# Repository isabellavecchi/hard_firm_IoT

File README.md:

# hard_firm_IoT
An WiFi connected Sound System with Alarm Clock, and real-time weather info

O projeto de firmware oficial é o wakeNdance. 

A tabela de partição da memoria, que substituí manualmente se encontra na pasta raiz de firmware.

Também foi necessário mudar a configuração de memória manualmente, mudei para 16Mbytes.

Este projeto foi inicializado na disciplina de "Hardware e Firmware - IoT" da UFU, e continuei o desenvolvimento para portifólio.

A placa utilizada foi a ESP32-S3 OTG.

Features:
  
  - Wi-Fi com conexão controlada;
  
  - serviço web construído de forma a dar manutenção facilitada;
  
  - tasks dos botões contruída, mas aguardando a função de leitura do cartão ser concluída, para ter as funcionalidades costuradas;
  
  - freeRTOS, com controle de queue entre tasks;
  
  - servidor HTTP controlando o serviço web;
  
  - back-end e front-end funcionando;
  
  - socket NTP;
  
  - LED atualizando de acordo com o status da conexão;
  
  - display OLED 1306 funcionando, e com funções default, como o botão, aguardando a resolução de bugs do DMA;
  
  - features implementadas no modelo POO.

To finish:
  
  - trocar a saída de som I2S por PDM, pelo fato de o módulo sendo utilizado, não ter tradução de I2S;
  
  - testar o DMA após a saída;
  
  - assim que as 2 camadas supracitadas estiverem funciando adequadamente, convertê-las para POO.

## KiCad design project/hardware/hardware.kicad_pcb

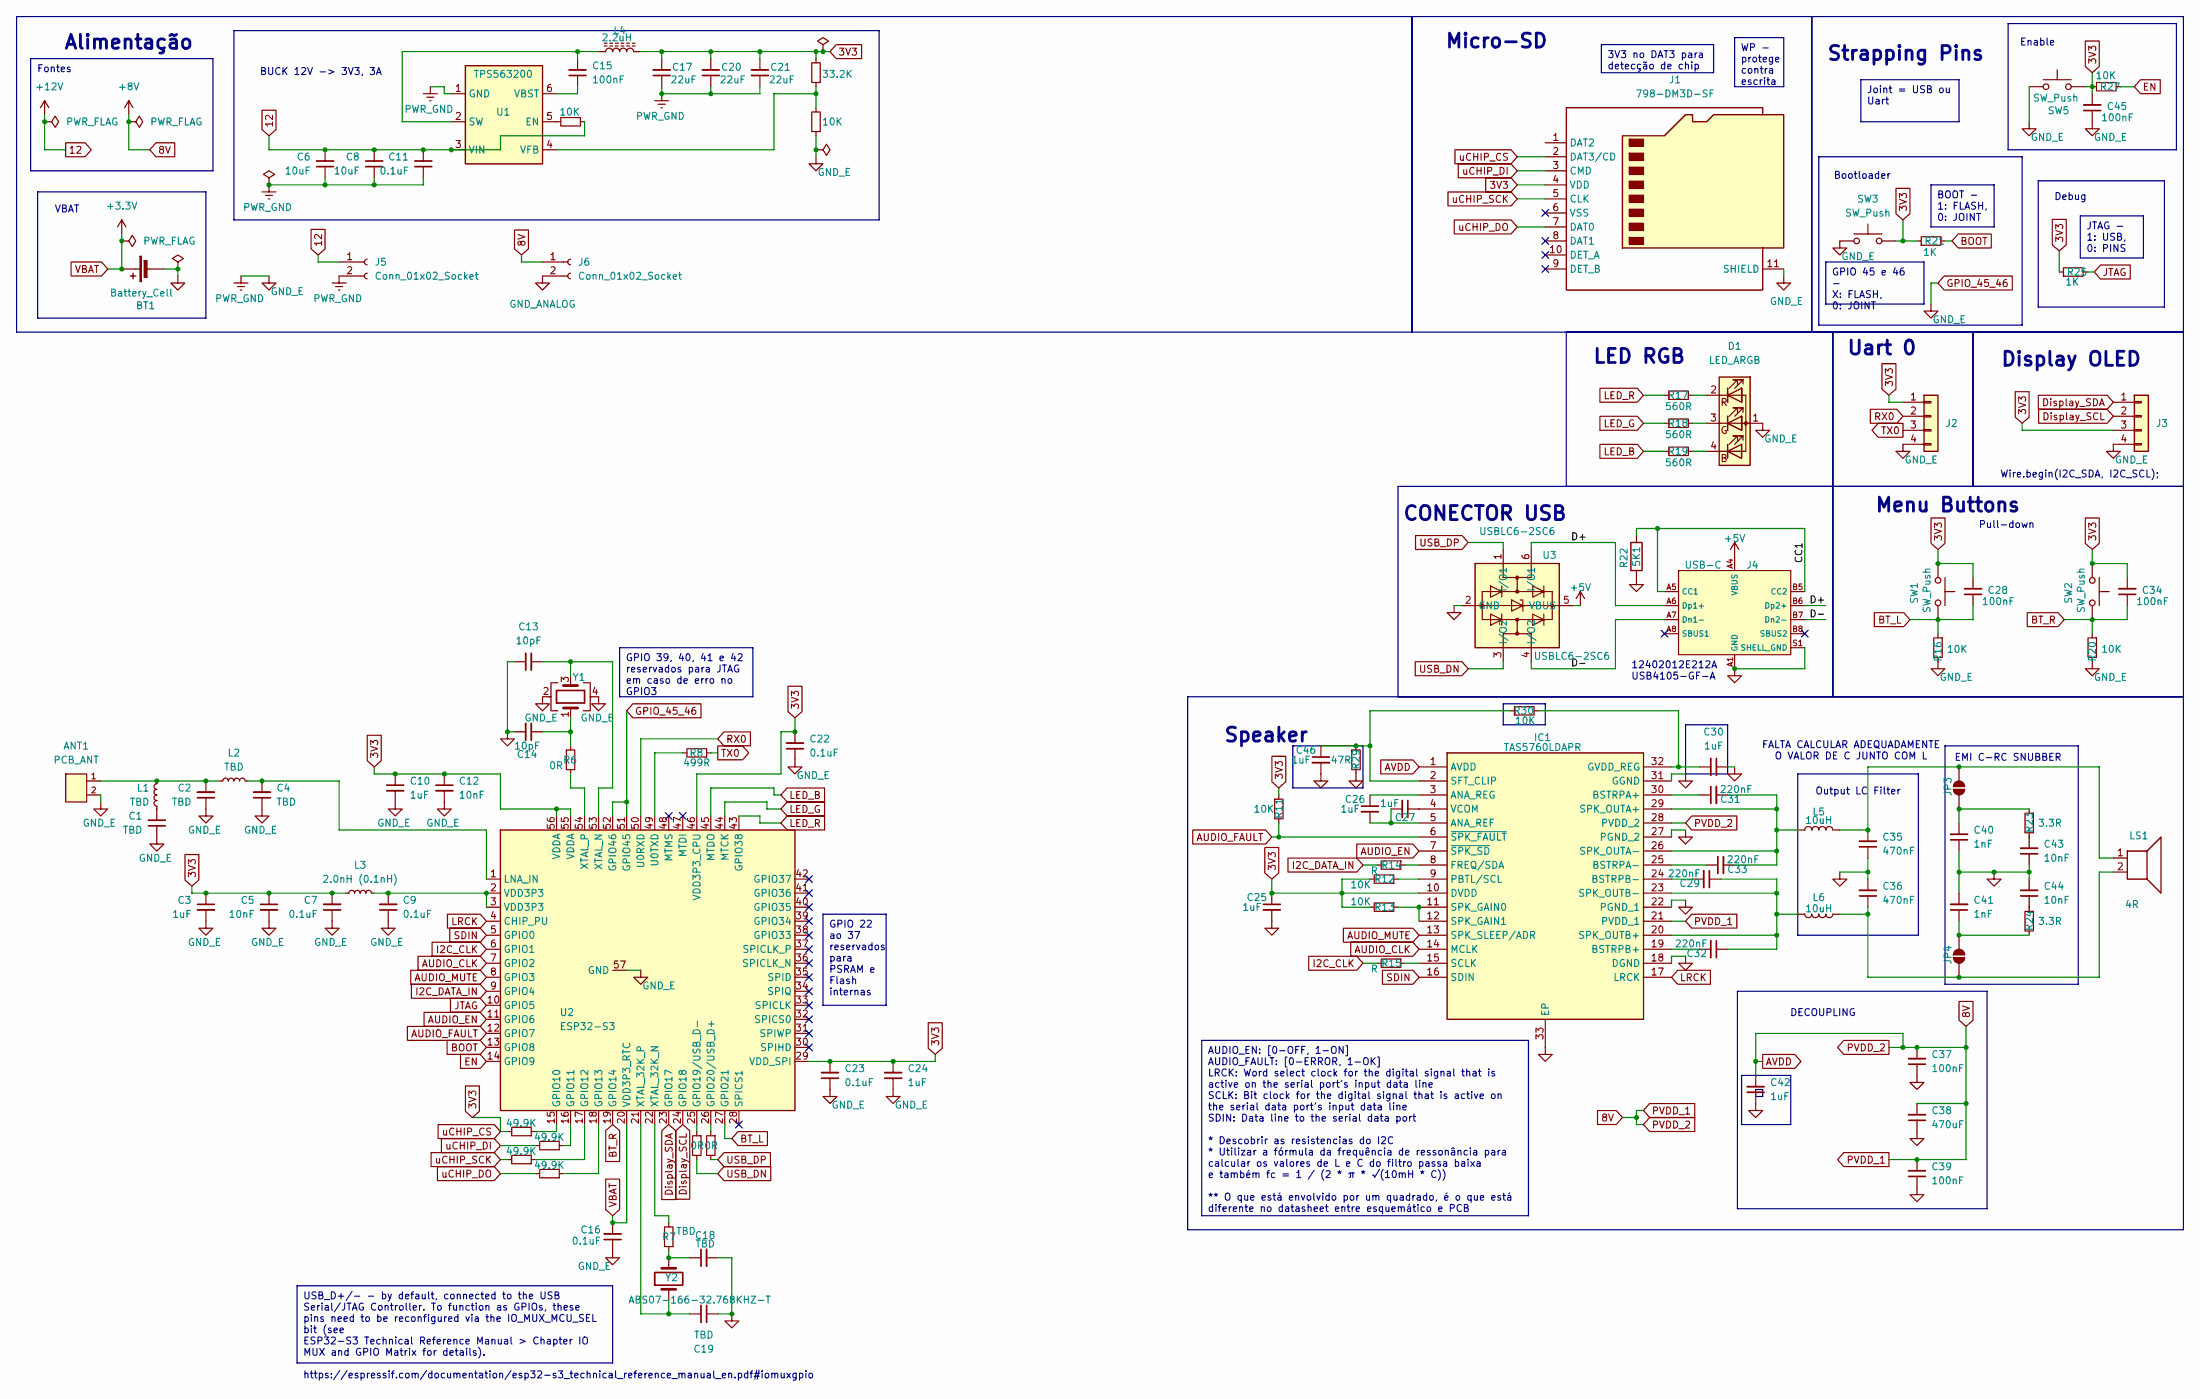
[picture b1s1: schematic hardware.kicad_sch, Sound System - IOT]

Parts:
ANT1: PCB_ANT; Texas_SWRA117D_2.4GHz_Left
BT1: Battery_Cell
C1, C2, C4, C18, C19: TBD; C_0402_1005Metric
C3, C10, C24, C25, C26, C27, C30, C42, C46: 1uF; C_0402_1005Metric
C5, C12, C43, C44: 10nF; C_0402_1005Metric
C6, C8: 10uF; C_0805_2012Metric_Pad1.18x1.45mm_HandSolder
C7, C9, C11, C16, C22, C23: 0.1uF; C_0402_1005Metric
C13, C14: 10pF; C_0402_1005Metric
C15: 100nF; C_0805_2012Metric_Pad1.18x1.45mm_HandSolder
C17, C20, C21: 22uF; C_0603_1608Metric_Pad1.08x0.95mm_HandSolder
C28, C34, C37, C39, C45: 100nF; C_0402_1005Metric
C29, C31, C32, C33: 220nF; C_0402_1005Metric
C35, C36: 470nF; C_0402_1005Metric
C38: 470uF; C_0402_1005Metric
C40, C41: 1nF; C_0402_1005Metric
D1: LED_ARGB; PinSocket_1x04_P1.27mm_Vertical_SMD_Pin1Left
IC1: TAS5760LDAPR; HTSSOP-32-1EP_6.1x11mm_P0.65mm_EP5.2x11mm_Mask4.11x4.36mm_T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; Mouser Part Number 595-TAS5760LDAPR
J1: 798-DM3D-SF; microSD_HC_Hirose_DM3D-SF; Mouser Part Number 523-GMC020080HR
J2, J3: Conn_01x04; PinSocket_1x04_P1.27mm_Vertical_SMD_Pin1Left
J4: USB-C; USB_C_Receptacle_XKB_U262-16XN-4BVC11
J5, J6: Conn_01x02_Socket; PinSocket_2x01_P2.54mm_Vertical_SMD
JP3, JP4: SolderJumper_2_Open; SolderJumper-2_P1.3mm_Open_RoundedPad1.0x1.5mm
L1, L2: TBD; L_0402_1005Metric
L3: 2.0nH (0.1nH); L_0402_1005Metric
L4: 2.2uH; L_TDK_VLS6045EX_VLS6045AF
L5, L6: 10uH; L_0402_1005Metric
LS1: 4R; PinSocket_2x01_P2.54mm_Vertical_SMD
R1, R2, R3, R4: 49.9K; R_0402_1005Metric
R5, R10, R11, R12, R13, R16, R20, R27, R30: 10K; R_0201_0603Metric_Pad0.64x0.40mm_HandSolder
R6, R26, R28: 0R; R_0402_1005Metric
R7: TBD; R_0402_1005Metric
R8: 499R; R_0402_1005Metric
R9: 33.2K; R_0402_1005Metric
R14, R15: R; R_0201_0603Metric_Pad0.64x0.40mm_HandSolder
R17, R18, R19: 560R; R_0402_1005Metric
R21, R25: 1K; R_0402_1005Metric
R22: 5K1; R_0402_1005Metric
R23, R24: 3.3R; R_0402_1005Metric
R29: 47R; R_0201_0603Metric_Pad0.64x0.40mm_HandSolder
SW1, SW2, SW3, SW5: SW_Push; SW_SPST_PTS810
U1: TPS563200; SOT-23-6
U2: ESP32-S3; QFN-56-1EP_7x7mm_P0.4mm_EP4x4mm
U3: USBLC6-2SC6; SOT95P280X145-6N
Y1: ECS-400-10-36B2-CKM-TR; Crystal_SMD_2520-4Pin_2.5x2.0mm
Y2: ABS07-166-32.768KHZ-T; Crystal_SMD_MicroCrystal_CC7V-T1A-2Pin_3.2x1.5mm_HandSolder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

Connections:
3V3: C3.1, C5.1, C7.2, C10.1, C12.1, C17.2, C20.2, C21.2, C22.2, C23.2, C24.2, C25.1, C28.2, C34.2, C45.2, IC1.10 (DVDD), J1.2 (DAT3/CD), J1.4 (VDD), J2.1, J3.3, L3.1, L4.2, R1.2, R9.2, R11.1, R12.2, R13.2, R21.1, R25.1, R27.1, SW1.1, SW2.1, SW3.2, SW5.2, U2.29 (VDD_SPI), U2.46 (VDD3P3_CPU), U2.55 (VDDA), U2.56 (VDDA)
8V: C37.2, C38.2, C39.2, C42.2, IC1.1 (AVDD), IC1.21 (PVDD_1), IC1.28 (PVDD_2), J6.1
12: C6.2, C8.2, C11.2, J5.1, R5.1, U1.3 (VIN)
+5V: J4.A4 (VBUS), J4.A9 (VBUS), J4.B4 (VBUS), J4.B9 (VBUS), U3.5 (VBUS)
/CC1: J4.A5 (CC1), J4.B5 (CC2), R22.1
/D+: J4.A6 (Dp1+), J4.B6 (Dp2+), U3.6 (I/O1)
/D-: J4.A7 (Dn1-), J4.B7 (Dn2-), U3.4 (I/O2)
AUDIO_CLK: IC1.14 (MCLK), U2.7 (GPIO2)
AUDIO_EN: IC1.7 (~SPK_SD), U2.11 (GPIO6)
AUDIO_FAULT: IC1.6 (~SPK_FAULT), R11.2, U2.12 (GPIO7)
AUDIO_MUTE: IC1.13 (SPK_SLEEP/ADR), U2.8 (GPIO3)
BOOT: R21.2, U2.13 (GPIO8)
BT_L: C28.1, R16.1, SW1.2, U2.27 (GPIO21)
BT_R: C34.1, R20.1, SW2.2, U2.19 (GPIO14)
Display_SCL: J3.2, U2.24 (GPIO18)
Display_SDA: J3.1, U2.23 (GPIO17)
EN: R27.2, U2.14 (GPIO9)
GND: BT1.2 (-), C13.1, C14.2, C18.2, C19.1, C25.2, C46.2, J4.A1 (GND), J4.A12 (GND), J4.B1 (GND), J4.B12 (GND), J4.S1 (SHELL_GND), R22.2, R29.2, U3.2 (GND)
GND_ANALOG: C30.1, C35.1, C36.2, C37.1, C38.1, C39.1, C40.1, C41.2, C42.1, C43.1, C44.2, IC1.18 (DGND), IC1.22 (PGND_1), IC1.27 (PGND_2), IC1.31 (GGND), IC1.33 (EP), J6.2
GPIO_45_46: ANT1.2, C1.1, C2.1, C3.2, C4.1, C5.2, C6.1, C7.1, C8.1, C9.1, C10.2, C11.1, C12.2, C16.1, C17.1, C20.1, C21.1, C22.1, C23.1, C24.1, C45.1, D1.1 (A), J1.11 (SHIELD), J2.4, J3.4, J5.2, R10.1, R16.2, R20.2, SW3.1, SW5.1, U1.1 (GND), U2.51 (GPIO45), U2.52 (GPIO46), U2.57 (GND), Y1.2, Y1.4
I2C_CLK: R15.2, U2.6 (GPIO1)
I2C_DATA_IN: R14.2, U2.9 (GPIO4)
JTAG: R25.2, U2.10 (GPIO5)
LED_B: R19.1, U2.45 (MTDO)
LED_G: R18.1, U2.44 (MTCK)
LED_R: R17.1, U2.43 (GPIO38)
LRCK: IC1.17 (LRCK), U2.4 (CHIP_PU)
unnamed: ANT1.1, C2.2, L1.1, L2.1
unnamed: C1.2, L1.2
unnamed: C9.2, L3.2, U2.2 (VDD3P3), U2.3 (VDD3P3)
unnamed: C14.1, R6.1, Y1.1
unnamed: C18.1, R7.1, Y2.2
unnamed: C43.2, R23.2
unnamed: C44.1, R24.1
unnamed: D1.4 (BK), R19.2
unnamed: D1.3 (GK), R18.2
unnamed: D1.2 (RK), R17.2
unnamed: C26.2, C27.2, IC1.5 (ANA_REF)
unnamed: C26.1, IC1.3 (ANA_REG)
unnamed: C31.1, IC1.30 (BSTRPA+)
unnamed: C33.1, IC1.25 (BSTRPA-)
unnamed: C32.2, IC1.19 (BSTRPB+)
unnamed: C29.2, IC1.24 (BSTRPB-)
unnamed: IC1.8 (FREQ/SDA), R14.1
unnamed: C30.2, IC1.32 (GVDD_REG), R30.2
unnamed: IC1.9 (PBTL/SCL), R12.1
unnamed: IC1.15 (SCLK), R15.1
unnamed: C46.1, IC1.2 (SFT_CLIP), R29.1, R30.1
unnamed: IC1.11 (SPK_GAIN0), IC1.12 (SPK_GAIN1), R13.1
unnamed: C31.2, C33.2, IC1.26 (SPK_OUTA-), IC1.29 (SPK_OUTA+), L5.1
unnamed: C29.1, C32.1, IC1.20 (SPK_OUTB+), IC1.23 (SPK_OUTB-), L6.1
unnamed: C27.1, IC1.4 (VCOM)
unnamed: C40.2, JP3.1 (A), R23.1
unnamed: C35.2, JP3.2 (B), L5.2, LS1.1
unnamed: C36.1, JP4.1 (A), L6.2, LS1.2
unnamed: C41.1, JP4.2 (B), R24.2
unnamed: R5.2, U1.5 (EN)
unnamed: C15.2, L4.1, U1.2 (SW)
unnamed: C15.1, U1.6 (VBST)
unnamed: R9.1, R10.2, U1.4 (VFB)
unnamed: R1.1, U2.15 (GPIO10)
unnamed: R3.1, U2.16 (GPIO11)
unnamed: R2.1, U2.17 (GPIO12)
unnamed: R4.1, U2.18 (GPIO13)
unnamed: R26.1, U2.25 (GPIO19/USB_D-)
unnamed: R28.1, U2.26 (GPIO20/USB_D+)
unnamed: C4.2, L2.2, U2.1 (LNA_IN)
unnamed: R8.2, U2.49 (U0TXD)
unnamed: R7.2, U2.22 (XTAL_32K_N)
unnamed: C19.2, U2.21 (XTAL_32K_P), Y2.1
unnamed: C13.2, U2.53 (XTAL_N), Y1.3
unnamed: R6.2, U2.54 (XTAL_P)
RX0: J2.2, U2.50 (U0RXD)
SDIN: IC1.16 (SDIN), U2.5 (GPIO0)
TX0: J2.3, R8.1
USB_DN: R26.2, U3.3 (I/O2)
USB_DP: R28.2, U3.1 (I/O1)
VBAT: BT1.1 (+), C16.2, U2.20 (VDD3P3_RTC)
uCHIP_DI: J1.3 (CMD), R3.2
uCHIP_DO: J1.7 (DAT0), R4.2
uCHIP_SCK: J1.5 (CLK), R2.2

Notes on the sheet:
WP - protege contra escrita
Joint = USB ou Uart
GPIO 39, 40, 41 e 42 reservados para JTAG em caso de erro no GPIO3
USB_D+/- - by default, connected to the USB Serial/JTAG Controller. To function as GPIOs, these pins need to be reconfigured via the IO_MUX_MCU_SEL bit (see ESP32-S3 Technical Reference Manual > Chapter IO MUX and GPIO Matrix for details). https://espressif.com/documentation/esp32-s3_technical_refe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
AUDIO_EN: [0-OFF, 1-ON] AUDIO_FAULT: [0-ERROR, 1-OK] LRCK: Word select clock for the digital signal that is active on the serial port's input data line SCLK: Bit clock for the digital signal that is active on the serial data port's input data line SDIN: Data line to the serial data port * Descobrir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
JTAG - 1: USB, 0: PINS
GPIO 45 e 46 - X: FLASH, 0: JOINT
BOOT - 1: FLASH, 0: JOINT
GPIO 22 ao 37 reservados para PSRAM e Flash internas
3V3 no DAT3 para detecção de chip
Micro-SD
LED RGB
EMI C-RC SNUBBER
Display OLED
Wire.begin(I2C_SDA, I2C_SCL);
Enable
Menu Buttons
FALTA CALCULAR ADEQUADAMENTE O VALOR DE C JUNTO COM L
Bootloader
CONECTOR USB
VBAT
DECOUPLING
Pull-down
BUCK 12V -> 3V3, 3A
Speaker
12402012E212A USB4105-GF-A
Strapping Pins
Alimentação
Debug
Uart 0
Output LC Filter
Fontes

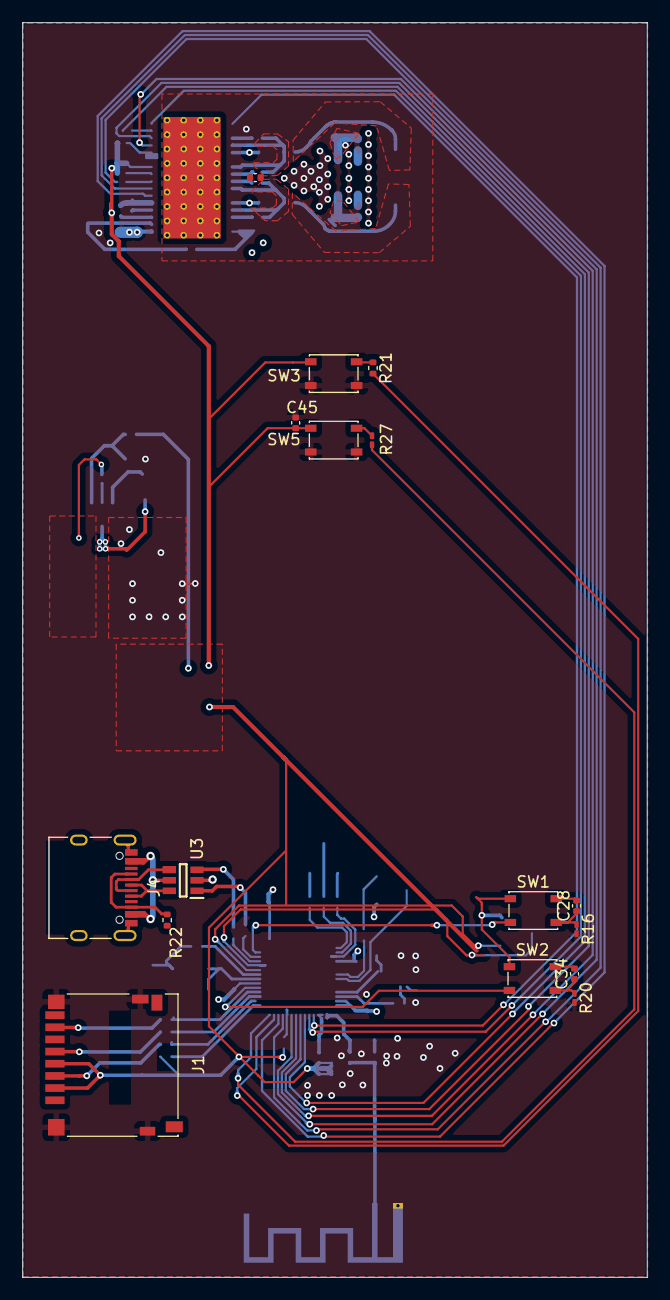
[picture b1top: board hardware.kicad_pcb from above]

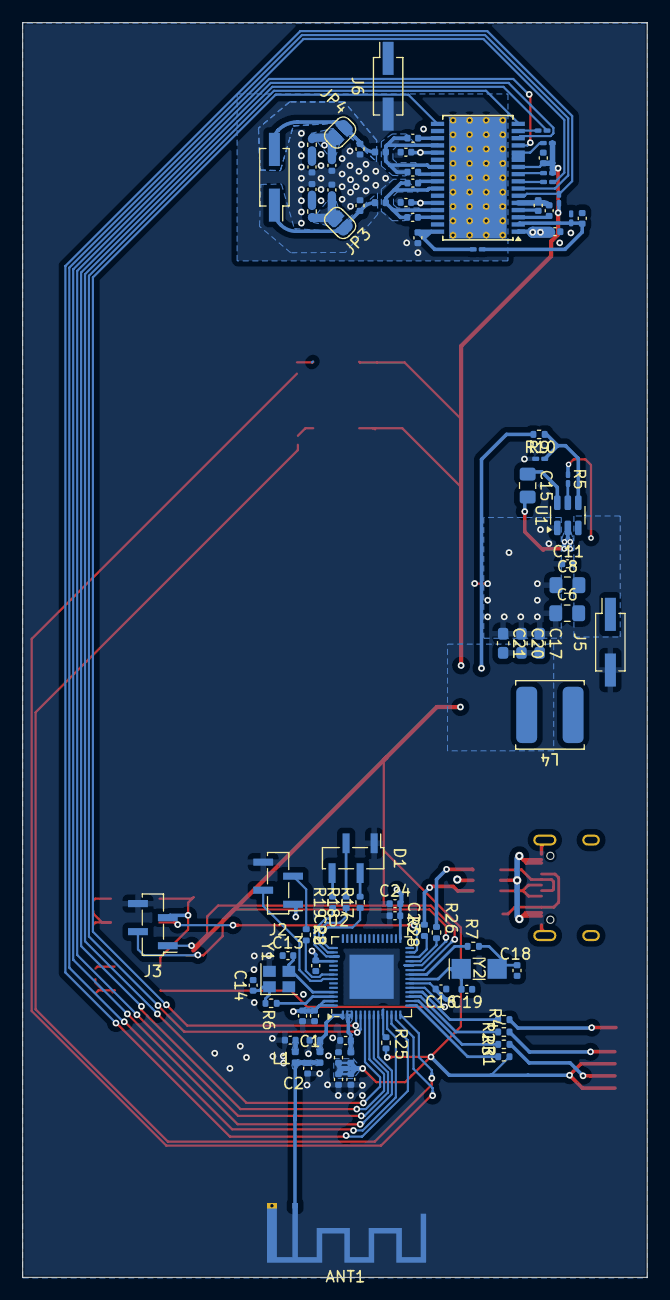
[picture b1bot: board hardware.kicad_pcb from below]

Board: 4 copper layers, 56.5 x 113.5 mm, 103 parts (87 on the bottom side), 81 nets.

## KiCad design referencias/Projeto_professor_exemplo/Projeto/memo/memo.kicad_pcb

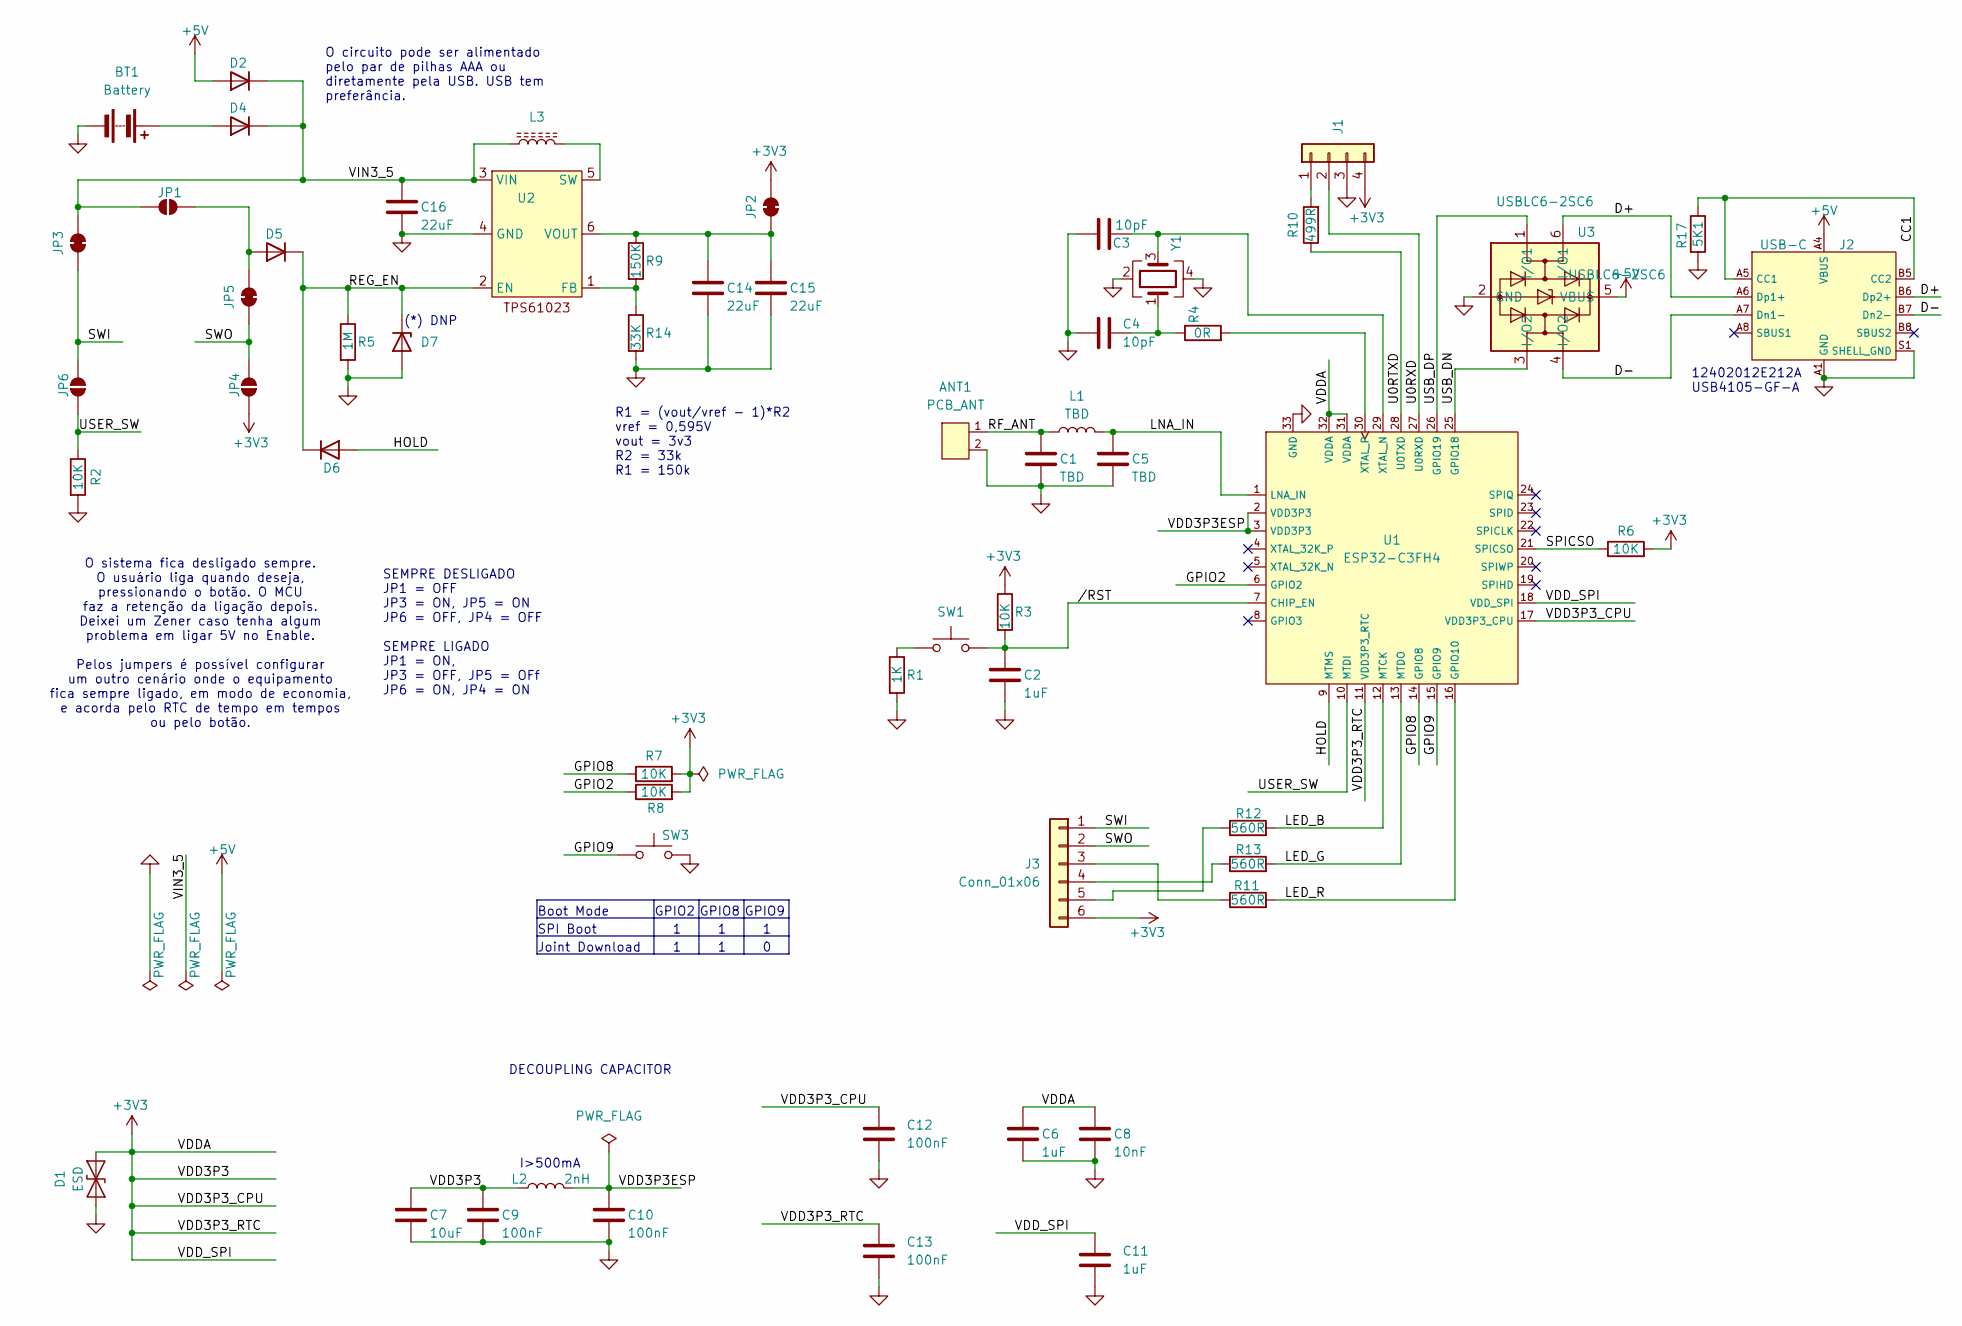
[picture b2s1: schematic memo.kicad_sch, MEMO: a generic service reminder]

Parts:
ANT1: PCB_ANT; Texas_SWRA117D_2.4GHz_Left
BT1: Battery; BatteryHolder_2xAAA
C1, C5: TBD; C_0402_1005Metric
C2, C6, C11: 1uF; C_0402_1005Metric
C3, C4: 10pF; C_0402_1005Metric
C7: 10uF; C_0603_1608Metric
C8: 10nF; C_0402_1005Metric
C9, C10, C12, C13: 100nF; C_0402_1005Metric
C14, C15, C16: 22uF; C_0603_1608Metric
D1: ESD; D_SOD-923
D2, D4, D5, D6, D7: D; D_SOD-123
J1: Conn_01x04; PinHeader_1x04_P1.27mm_Vertical
J2: USB-C; USB_C_Receptacle_XKB_U262-16XN-4BVC11
J3: Conn_01x06; PinHeader_1x06_P1.27mm_Vertical
JP1, JP4, JP6: SolderJumper_2_Open; SolderJumper-2_P1.3mm_Open_RoundedPad1.0x1.5mm
JP2, JP3, JP5: SolderJumper_2_Bridged; SolderJumper-2_P1.3mm_Bridged_RoundedPad1.0x1.5mm
L1: TBD; L_0402_1005Metric
L2: 2nH; L_0402_1005Metric
L3: L_Ferrite; XEL4030101MED
R1: 1K; R_0603_1608Metric
R2, R3, R6, R7, R8: 10K; R_0402_1005Metric
R4: 0R; R_0402_1005Metric
R5: 1M; R_0402_1005Metric
R9: 150K; R_0402_1005Metric
R10: 499R; R_0603_1608Metric
R11, R12, R13: 560R; R_0402_1005Metric
R14: 33K; R_0402_1005Metric
R17: 5K1; R_0402_1005Metric
SW1, SW3: SW_Push; SW_SPST_PTS810
U1: ESP32-C3FH4; QFN50P500X500X90-33N-D
U2: SOT-563
U3: USBLC6-2SC6; SOT95P280X145-6N
Y1: ECS-400-10-36B2-CKM-TR; Crystal_SMD_2520-4Pin_2.5x2.0mm

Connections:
+3V3: C6.1, C7.1, C8.1, C9.1, C11.1, C12.1, C13.1, D1.2 (A2), J1.4, J3.6, JP2.2 (B), JP4.1 (A), L2.1, R3.1, R6.2, R7.2, R8.2, U1.11 (VDD3P3_RTC), U1.17 (VDD3P3_CPU), U1.18 (VDD_SPI), U1.31 (VDDA), U1.32 (VDDA)
+5V: D2.2 (A), J2.A4 (VBUS), J2.A9 (VBUS), J2.B4 (VBUS), J2.B9 (VBUS), U3.5 (VBUS)
/CC1: J2.A5 (CC1), J2.B5 (CC2), R17.1
/D+: J2.A6 (Dp1+), J2.B6 (Dp2+), U3.6 (I/O1)
/D-: J2.A7 (Dn1-), J2.B7 (Dn2-), U3.4 (I/O2)
/GPIO2: R8.1, U1.6 (GPIO2)
/GPIO8: R7.1, U1.14 (GPIO8)
/GPIO9: SW3.1, U1.15 (GPIO9)
/HOLD: D6.2 (A), U1.9 (MTMS)
/LED_B: R12.2, U1.12 (MTCK)
/LED_G: R13.2, U1.13 (MTDO)
/LED_R: R11.2, U1.16 (GPIO10)
/LNA_IN: C5.1, L1.2, U1.1 (LNA_IN)
/REG_EN: D5.1 (K), D6.1 (K), D7.1 (K), R5.1, U2.2 (EN)
/RF_ANT: ANT1.1, C1.1, L1.1
/SPICSO: R6.1, U1.21 (SPICSO)
/SWI: J3.1, JP3.1 (A), JP6.2 (B)
/SWO: J3.2, JP4.2 (B), JP5.1 (A)
/U0RTXD: R10.1, U1.28 (U0TXD)
/U0RXD: J1.2, U1.27 (U0RXD)
/USB_DN: U1.25 (GPIO18), U3.3 (I/O2)
/USB_DP: U1.26 (GPIO19), U3.1 (I/O1)
/USER_SW: JP6.1 (A), R2.1, U1.10 (MTDI)
/VDD3P3ESP: C10.1, L2.2, U1.2 (VDD3P3), U1.3 (VDD3P3)
/VIN3_5: C16.1, D2.1 (K), D4.1 (K), JP1.1 (A), JP3.2 (B), L3.1, U2.3 (VIN)
//RST: C2.1, R3.2, SW1.2, U1.7 (CHIP_EN)
GND: ANT1.2, BT1.2 (-), C1.2, C2.2, C3.1, C4.2, C5.2, C6.2, C7.2, C8.2, C9.2, C10.2, C11.2, C12.2, C13.2, C14.2, C15.2, C16.2, D1.1 (A1), D7.2 (A), J1.3, J2.A1 (GND), J2.A12 (GND), J2.B1 (GND), J2.B12 (GND), J2.S1 (SHELL_GND), R1.2, R2.2, R5.2, R14.2, R17.2, SW3.2, U1.33 (GND), U2.4 (GND), U3.2 (GND), Y1.2, Y1.4
unnamed: BT1.1 (+), D4.2 (A)
unnamed: C4.1, R4.1, Y1.1
unnamed: D5.2 (A), JP1.2 (B), JP5.2 (B)
unnamed: J1.1, R10.2
unnamed: J3.3, R11.1
unnamed: J3.4, R13.1
unnamed: J3.5, R12.1
unnamed: C14.1, C15.1, JP2.1 (A), R9.1, U2.6 (VOUT)
unnamed: R1.1, SW1.1
unnamed: C3.2, U1.29 (XTAL_N), Y1.3
unnamed: R4.2, U1.30 (XTAL_P)
unnamed: R9.2, R14.1, U2.1 (FB)
unnamed: L3.2, U2.5 (SW)

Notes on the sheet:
12402012E212A USB4105-GF-A
SPI Boot
R1 = (vout/vref - 1)*R2 vref = 0,595V vout = 3v3 R2 = 33k R1 = 150k
O sistema fica desligado sempre. O usuário liga quando deseja, pressionando o botão. O MCU faz a retenção da ligação depois. Deixei um Zener caso tenha algum problema em ligar 5V no Enable. Pelos jumpers é possível configurar um outro cenário onde o equipamento fica sempre ligado, em modo de econom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
Joint Download
I>500mA
GPIO2
(*) DNP
SEMPRE DESLIGADO JP1 = OFF JP3 = ON, JP5 = ON JP6 = OFF, JP4 = OFF SEMPRE LIGADO JP1 = ON, JP3 = OFF, JP5 = OFf JP6 = ON, JP4 = ON
Boot Mode
GPIO8
DECOUPLING CAPACITOR
GPIO9
O circuito pode ser alimentado pelo par de pilhas AAA ou diretamente pela USB. USB tem preferância.

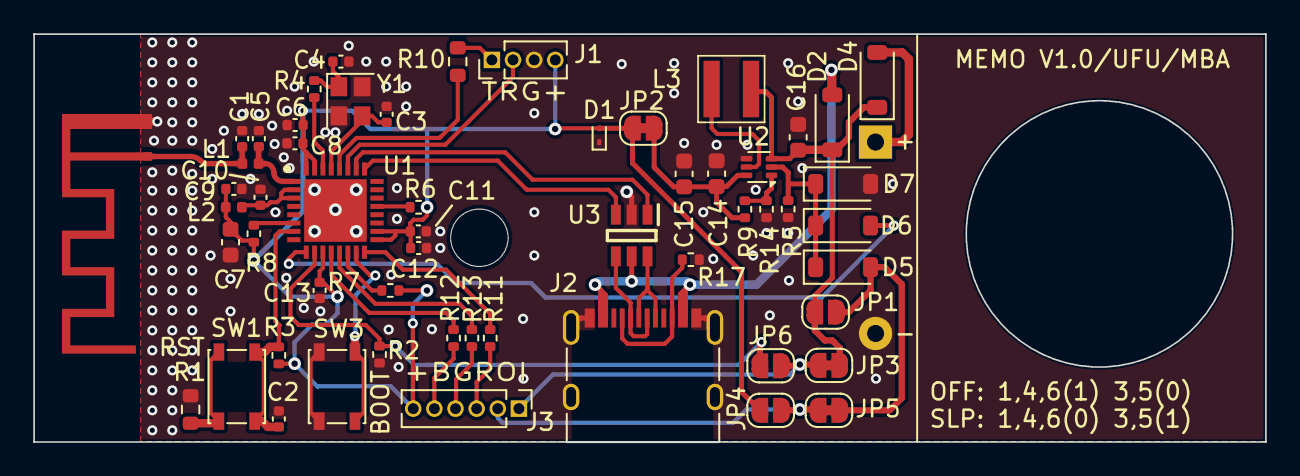
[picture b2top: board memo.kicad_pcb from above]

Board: 4 copper layers, 74.0 x 24.5 mm, 57 parts (1 on the bottom side), 40 nets.

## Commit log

2024-09-25 some drafts I would like to keep - 2 sounds amplifiers; external flash and PSRAM; and the beggining of a buck converter
2024-09-25 schematic - faltando o RTC clock, e conectar os I2C's num so canal
2024-09-30 atualizando alguns footprints; começando o desenho da placa
2024-10-01 RTC footprint; removed 2 buttons, an will remove more stuff to get the USB back
2024-10-05 esquemático com JTAG usb adicionada; preferi deixar o monitor numa i2c separada da i2c do amplificador de audio - para nao correr o risco de ao diminuir o volume buggar a tela
2024-10-06 sound components placed - there were some differences between layout and schematic on the amplifier documentation. They are emphasized by squares on schematic
2024-10-06 roteamentos do amplificador, perifericos agrupados
2024-10-06 desacoplamento
2024-10-06 cartao de memoria e usb
2024-10-07 coloquei a antena para cima para liberar espaço para o amplificador de som; adicionei algumas vias de terra
2024-10-07 realocando estruturas
2024-10-07 footprint socket 01x04 atualizado - partiu casa
2024-10-07 antes da aula
2024-10-07 codigo teste da aula passada
2024-10-07 mudando a estrutura de arquivos e adicionando o projeto hello_world no repositorio de aulas
2024-10-07 agora sim, dei commit da pasta errada
2024-10-08 colocando um projeto RTOS dentro do exemplo da esp
2024-10-26 trying out the s3 board
2024-10-30 structure of project
2024-11-08 adding refs
2024-11-09 wifi conectando
2024-11-09 separating the model_main, so that it is not the main anymore
2024-11-09 removing some tests that went wrong...
2024-11-18 codigo wakeNdance versao 3, com freeRTOS
2024-11-19 get wifi credentials
2024-11-19 curso na udemy sobre ESP-IDF IOT com freeRTOS
2024-11-20 menu de botão funcionando com freeRTOS, semaforo, interrupção e timer!
2024-11-20 adding global datetime and display OLED features - just drafts
2024-11-20 finally changed the 'planes'
2024-11-24 added the static functions headers on c file declaration area - sntp and display still not working
2024-11-24 alimentação
2024-11-24 realmente vou precisar desistir do SNTP, quebrando tudo que toca
2024-11-24 display oled
2024-11-25 faltando o plano de terra da antena
2024-11-25 plots
2024-11-25 Update README.md
    Adding instructions
2024-12-31 grabing in my fixed computer *-*
2025-01-01 display finally working! But only by terminal... and now my http request is bugged, because the header request is too long... gotta see that
2025-01-15 not just the POST is back to work, but also, now it is receiving data from body, as it should have been
2025-01-15 adding example from idf to repository, for tests purposes
2025-01-16 founded that my task of initializing my sntp is creating the task of initializing my sntp is creating the task of initializing my sntp is creating the task of initializing my sntp is creating the tas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
2025-01-23 boot button functioning well for menu, and not interrupted with polling
2025-01-23 all buttons functioning well - never give your computer without uploading your code! But I think this time the code is prettier than before.
2025-01-23 bye bye sntp
2025-01-23 forgot to save some files
2025-01-23 updating button topology on schematic
2025-01-25 NTP finally working! Menu started to be implemented on display. It guides the process of connecting to the sound box
2025-01-28 I2S working! Now let's begin with DMA o.O
2025-01-29 massive defeat - maybe will have to format computer to linux, and work on ESP-ADF
